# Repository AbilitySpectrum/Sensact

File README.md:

## The Sensact Hub
### An Arduino shield with analog inputs and IR and relay outputs
### - with generic 'sensing' and 'acting' functions configurable by software

#### Features

1. a shield that is compatible with the Arduino board
2. Arduino code that works in tandem with a web based app
3. The web-based app configures the Arduino+Sensact combo
4. Once configured, the combo may be plugged into any USB device for access control
5. The shield also has on-board IR transceivers and is Bluetooth capable

#### Motivation

Existing switch controls for computer users with physical impairment tend to be specialized and expensive. They general use one kind of sensors and have restricted functionality.

We provide a generic device that allows the user to experiment with different sensors, to find something that works best for him. We provide on-board IR output, a socket for an optional Bluetooth board and also configurable key strokes for USB HID controls. 

The Sensact Hub brings together 3 analog inputs (one of them can be configured as an I2C input) and 2 relay outputs as well as HID, IR and Bluetooth outputs.

We use 3.5mm audio sockets to make it easy to swap different input sensors. The tip is VCC, sleeve is GND and Ring is Signal. The first socket can be used by an I2C device where the two rings are SDA and SCL.

#### Use cases

We have used a number of sensors: light, capacitive touch, microphone as touch detectors. The signal can be used to trigger a call bell on one of the relays. Or it can be used to send specific letters over USB to control a smartphone or tablet. With Bluetooth, the hub sends out the letters wirelessly. The IR transceivers can function as a remote control for TV.

We have also been able to plug in a 6DO gyroscope+accelerator module. The user can then use movements to control a mouse.

#### Compatibility:

Board v1 + Arduino v1 + Config v1 or /Serial_port_version

Board v2 + Arduino v1 + Config v1 or /Chrome_version

Board v2 + Arduino v2 + Config v2

#### Set up Config v1

The web-based configuration software is in the *configSensact* directory.

The web-based software requires a serial port server. Its binary is downloadable from <https://github.com/johnlauer/serial-port-json-server>. It is compatible with OSX, Linux and Windows.

#### Set up Config v2

The Config v2 is a Chrome App. The a production release would be downloadable as a Chrome App but it currently must be added as an extension. 

More Tools -> Extensions. Check "Developer Mode". Load unpacked extension. Direct it to the configSensactApp directory.

#### To do
Currently no IR capability.

#### Partners

This work is performed by volunteers and staff at Bruyère's Saint Vincent Hospital AAC Clinic and Nathan Lim from Carleton University, all in Ottawa. 

Bruyère, Carleton and Ability Spectrum are not responsible for the use of this material. Please attribute the source if you republish or use partiallly or in whole, using License below.

#### Disclaimer

All design and code are provided with no warranty whatsoever.

#### License
<https://github.com/abilityspectrum>

Copyright (c) 2015-2016 Ability Spectrum

Permission is hereby granted, free of charge, to any person obtaining a copy
of this software and associated documentation files (the "Software"), to deal
in the Software without restriction, including without limitation the rights
to use, copy, modify, merge, publish, distribute, sublicense, and/or sell
copies of the Software, and to permit persons to whom the Software is
furnished to do so, subject to the following conditions:

The above copyright notice and this permission notice shall be included in
all copies or substantial portions of the Software.

THE SOFTWARE IS PROVIDED "AS IS", WITHOUT WARRANTY OF ANY KIND, EXPRESS OR
IMPLIED, INCLUDING BUT NOT LIMITED TO THE WARRANTIES OF MERCHANTABILITY,
FITNESS FOR A PARTICULAR PURPOSE AND NONINFRINGEMENT. IN NO EVENT SHALL THE
AUTHORS OR COPYRIGHT HOLDERS BE LIABLE FOR ANY CLAIM, DAMAGES OR OTHER
LIABILITY, WHETHER IN AN ACTION OF CONTRACT, TORT OR OTHERWISE, ARISING FROM,
OUT OF OR IN CONNECTION WITH THE SOFTWARE OR THE USE OR OTHER DEALINGS IN
THE SOFTWARE.

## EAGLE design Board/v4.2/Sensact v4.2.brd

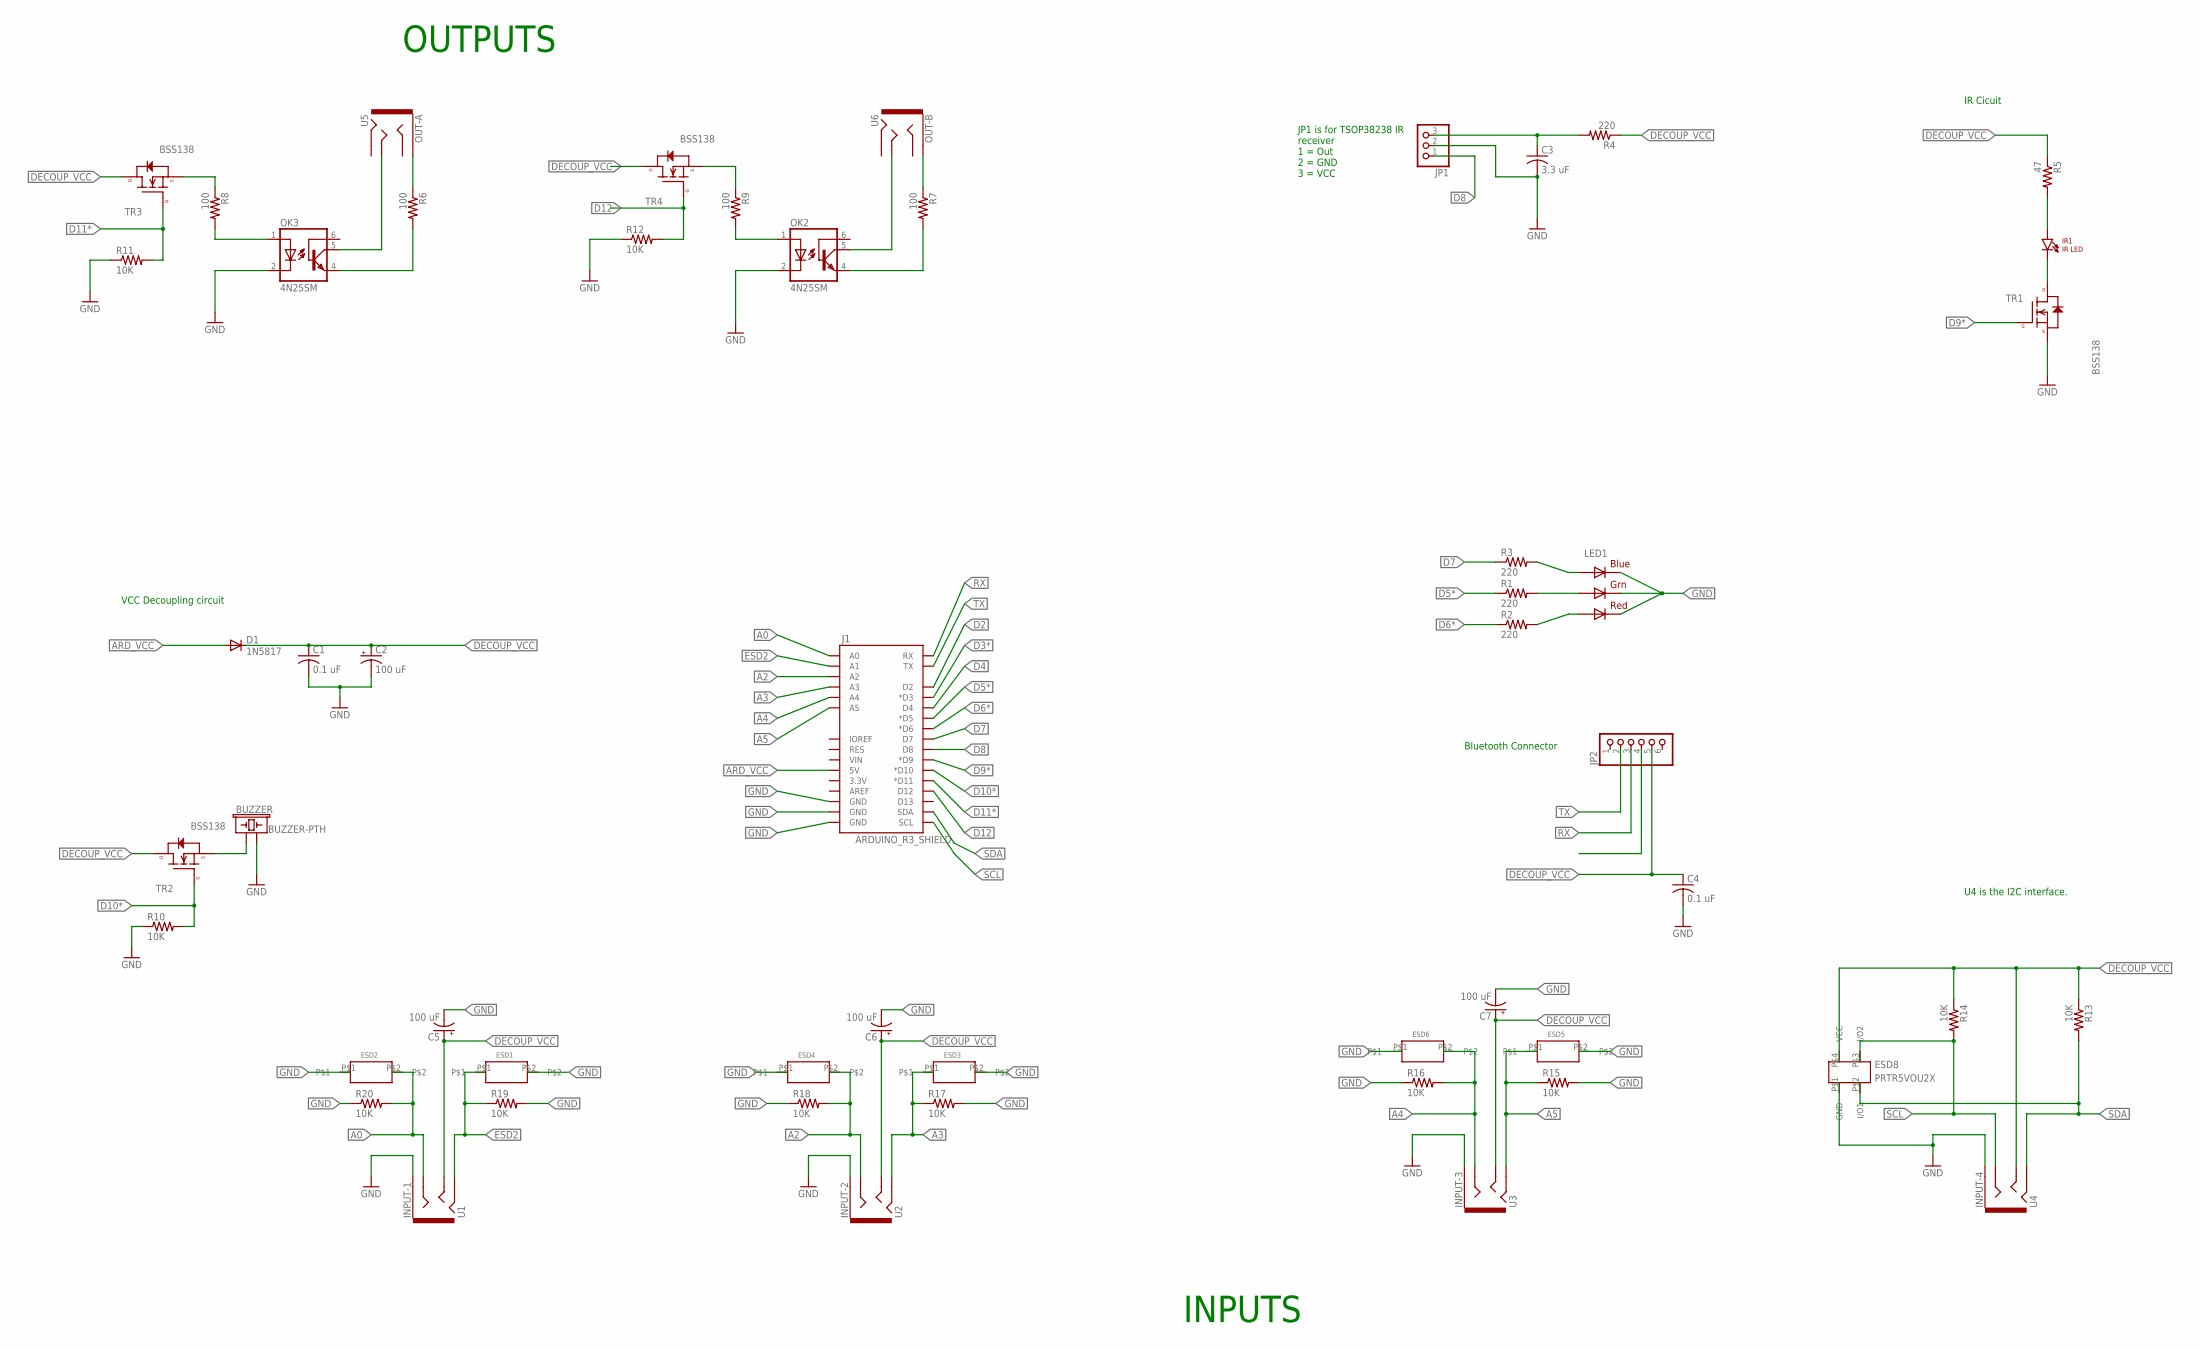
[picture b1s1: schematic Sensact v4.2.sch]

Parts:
BUZZER: BUZZER-PTH; BUZZER-12MM
C1, C4: 0.1 uF; C0805
C2, C5, C6, C7: 100 uF; PANASONIC_C
C3: 3.3 uF; C0805
D1: 1N5817; DO214AC
ESD1, ESD2, ESD3, ESD4, ESD5, ESD6: PESD5V0S1BA; SOD323
ESD8: PRTR5VOU2X; 215
INPUT-1: U1; AUDIO-JACK-TRRS-THRUHOLE
INPUT-2: U2; AUDIO-JACK-TRRS-THRUHOLE
INPUT-3: U3; AUDIO-JACK-TRRS-THRUHOLE
INPUT-4: U4; AUDIO-JACK-TRRS-THRUHOLE
IR1: IR LED; LTE-302
J1: ARDUINO_R3_SHIELD; UNO_R3_SHIELD
JP1: PINHD-1X3; 1X03
JP2: PINHD-1X6; 1X06
LED1: RGBLED5050
OK2, OK3: 4N25SM; DIL6-SMD
OUT-A: U5; AUDIO-JACK-TRRS-THRUHOLE
OUT-B: U6; AUDIO-JACK-TRRS-THRUHOLE
R1, R2, R3, R4: 220; 0805
R5: 47; 0805
R6, R7, R8, R9: 100; 0805
R10, R11, R12, R13, R14, R15, R16, R17, R18, R19, R20: 10K; 0805
TR1, TR2, TR3, TR4: BSS138; SOT23-3

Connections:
A0: ESD2.P$2, INPUT-1.RING1, J1.A0, R20.2
A2: ESD4.P$2, INPUT-2.RING1, J1.A2, R18.2
A3: ESD3.P$1, INPUT-2.RING2, J1.A3, R17.1
A4: ESD6.P$2, INPUT-3.RING1, J1.A4, R16.2
A5: ESD5.P$1, INPUT-3.RING2, J1.A5, R15.1
ARD_VCC: D1.A, J1.5V
D2: J1.D2
D3*: J1.D3 (*D3)
D4: J1.D4
D5*: J1.D5 (*D5), R1.1
D6*: J1.D6 (*D6), R2.1
D7: J1.D7, R3.1
D8: J1.D8, JP1.1
D9*: J1.D9 (*D9), TR1.1 (G)
D10*: J1.D10 (*D10), R10.2, TR2.1 (G)
D11*: J1.D11 (*D11), R11.2, TR3.1 (G)
D12: J1.D12, R12.2, TR4.1 (G)
DECOUP_VCC: C1.1, C2.+, C4.1, C5.+, C6.+, C7.+, D1.C, ESD8.P$4 (VCC), INPUT-1.TIP, INPUT-2.TIP, INPUT-3.TIP, INPUT-4.TIP, JP2.5, R4.1, R5.1, R13.1, R14.1, TR2.3 (D), TR3.3 (D), TR4.3 (D)
ESD2: ESD1.P$1, INPUT-1.RING2, J1.A1, R19.1
GND: BUZZER.- (2), C1.2, C2.-, C3.2, C4.2, ESD1.P$2, ESD2.P$1, ESD3.P$2, ESD4.P$1, ESD5.P$2, ESD6.P$1, ESD8.P$1 (GND), INPUT-1.SLEEVE (EARTH), INPUT-2.SLEEVE (EARTH), INPUT-3.SLEEVE (EARTH), INPUT-4.SLEEVE (EARTH), J1.GND@0 (GND), J1.GND@1 (GND), J1.GND@2 (GND), JP1.2, JP2.4, LED1.4 (BLUE_C), LED1.5 (RED_C), LED1.6 (GREEN_C), OK2.2 (C), OK3.2 (C), R10.1, R11.1, R12.1, R15.2, R16.1, R17.2, R18.1, R19.2, R20.1, TR1.2 (S)
unnamed: C3.1, JP1.3, R4.2
unnamed: OK3.4 (EMI), R6.2
unnamed: OK2.1 (A), R9.2
unnamed: OK3.1 (A), R8.2
unnamed: LED1.3 (BLUE_A), R3.2
unnamed: LED1.1 (GREEN_A), R1.2
unnamed: LED1.2 (RED_A), R2.2
unnamed: OK3.5 (COL), OUT-A.TIP
unnamed: OUT-A.SLEEVE (EARTH), R6.1
unnamed: OK2.5 (COL), OUT-B.TIP
unnamed: OUT-B.SLEEVE (EARTH), R7.1
unnamed: OK2.4 (EMI), R7.2
unnamed: IR1.A, R5.2
unnamed: IR1.C, TR1.3 (D)
unnamed: BUZZER.+ (1), TR2.2 (S)
unnamed: R9.1, TR4.2 (S)
unnamed: R8.1, TR3.2 (S)
RX: J1.RX, JP2.3
SCL: ESD8.P$3 (I/O2), INPUT-4.RING1, J1.SCL, R14.2
SDA: ESD8.P$2 (I/O1), INPUT-4.RING2, J1.SDA, R13.2
TX: J1.TX, JP2.2

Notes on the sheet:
JP1 is for TSOP38238 IR receiver 1 = Out 2 = GND 3 = VCC
VCC Decoupling circuit
U4 is the I2C interface.
OUTPUTS
INPUTS
Bluetooth Connector
IR Cicuit

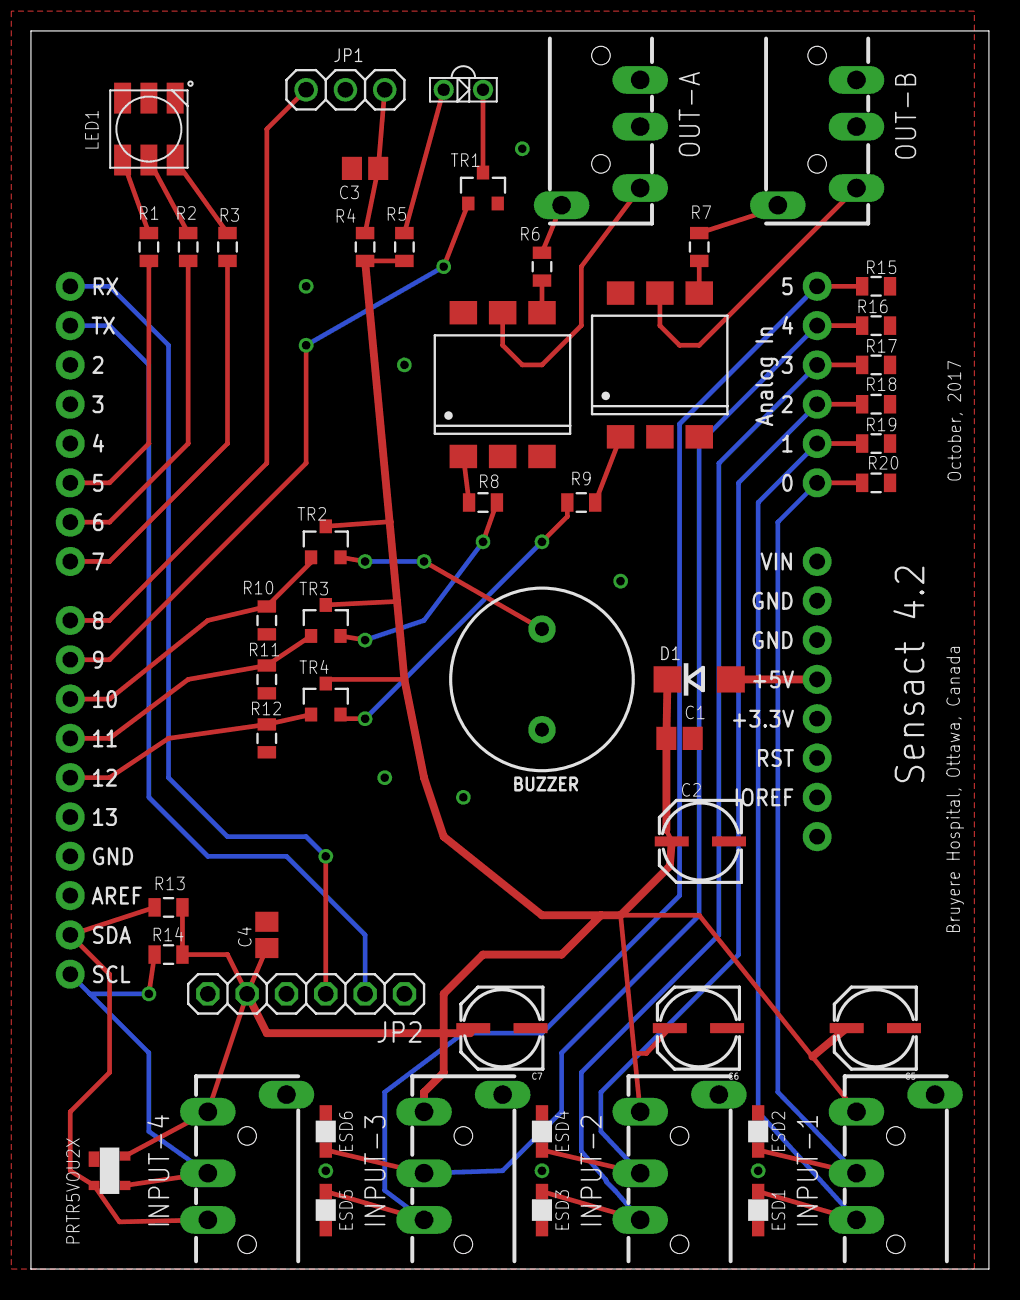
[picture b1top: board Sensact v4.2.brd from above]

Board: 2 copper layers, 61.9 x 80.0 mm, 53 parts (0 on the bottom side), 38 nets.

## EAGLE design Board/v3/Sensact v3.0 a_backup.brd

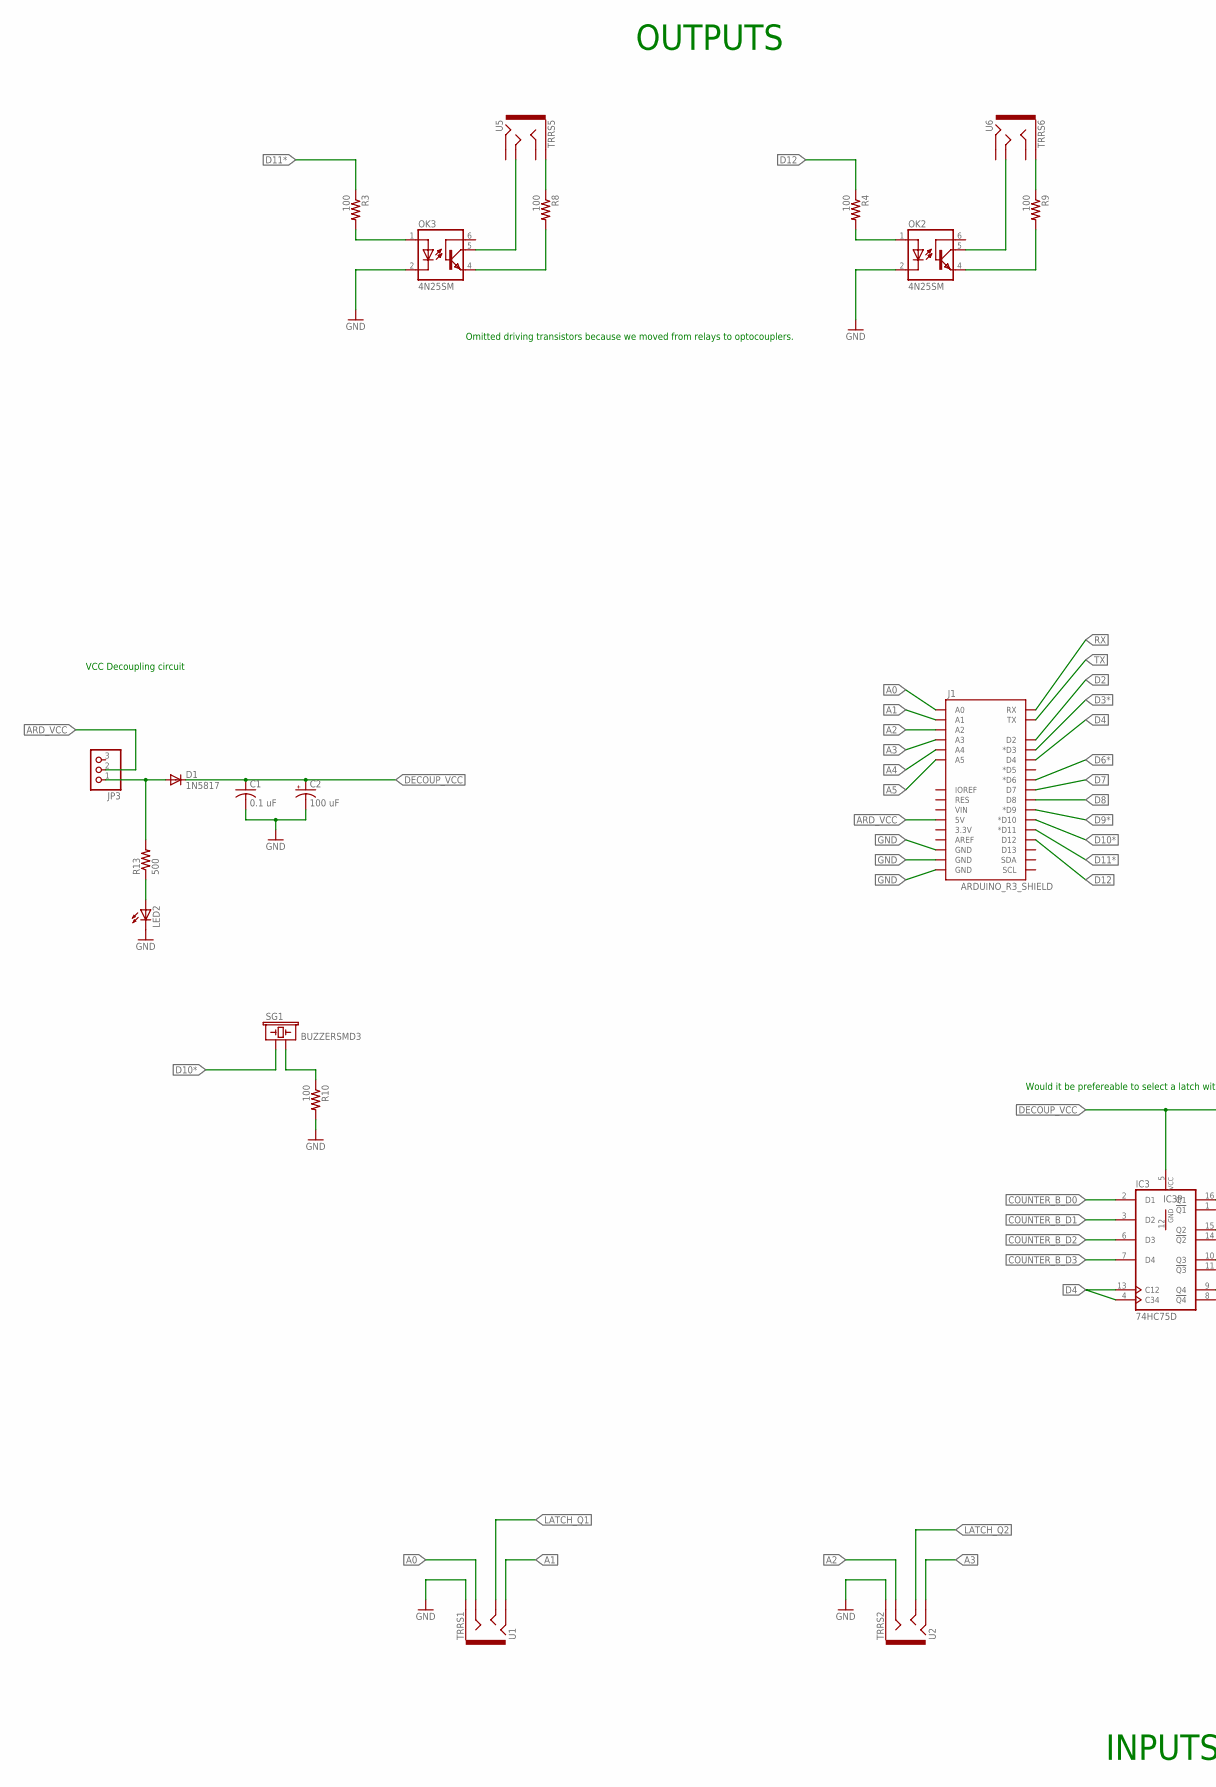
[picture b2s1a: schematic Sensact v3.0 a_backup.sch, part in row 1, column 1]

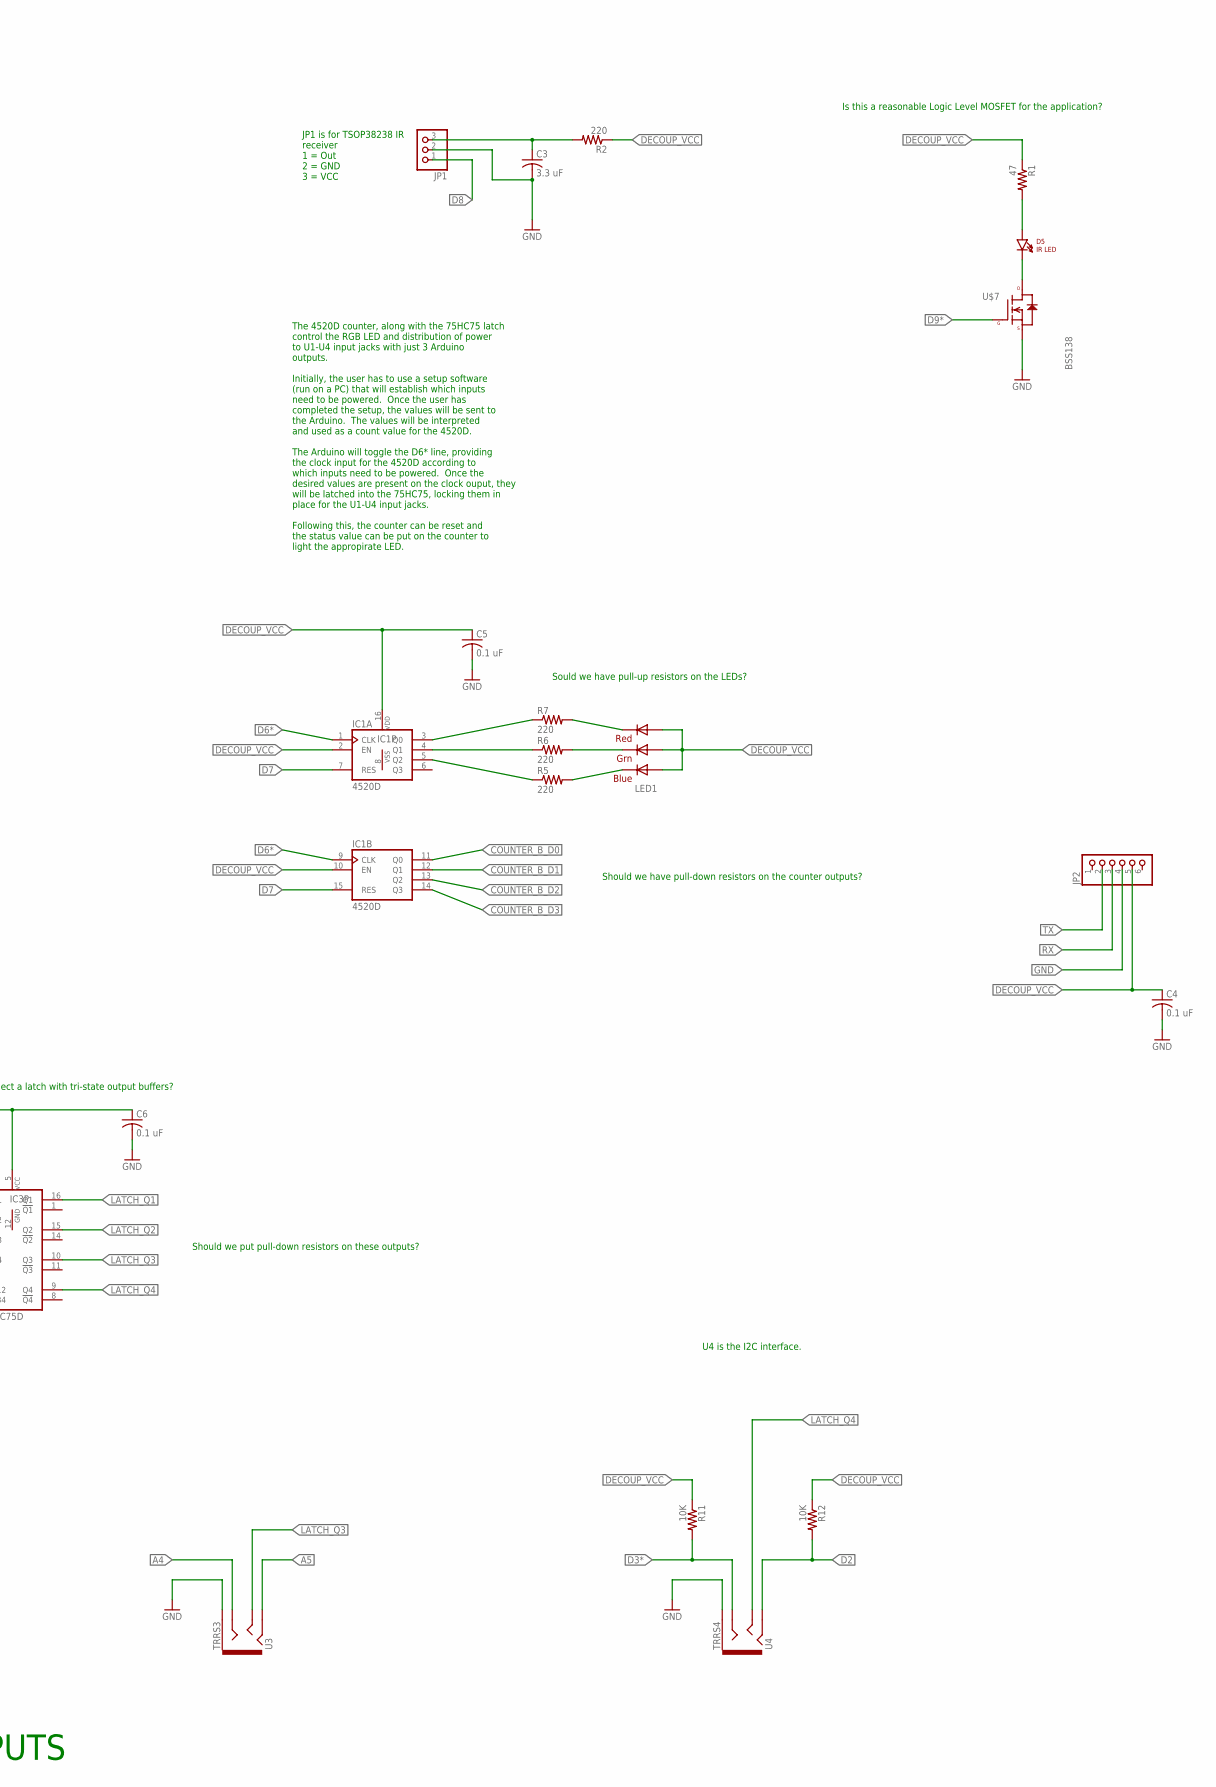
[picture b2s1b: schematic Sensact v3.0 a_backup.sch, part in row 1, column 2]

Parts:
C1, C4, C5, C6: 0.1 uF; C0805
C2: 100 uF; PANASONIC_C
C3: 3.3 uF; C0805
D1: 1N5817; DO214AC
D5: IR LED; LTE-302
IC1: 4520D; SO16
IC3: 74HC75D; SO16
J1: ARDUINO_R3_SHIELD; UNO_R3_SHIELD
JP1, JP3: PINHD-1X3; 1X03
JP2: PINHD-1X6; 1X06
LED1: RGBLED5050
LED2: LEDCHIPLED_0805; CHIPLED_0805
OK2, OK3: 4N25SM; DIL6-SMD
R1: 47; 0805
R2, R5, R6, R7: 220; 0805
R3, R4: 100; 0805
R8, R9, R10: 100; R0805
R11, R12: 10K; 0805
R13: 500; 0805
SG1: BUZZERSMD3; BUZZER-CMT1102
TRRS1: U1; AUDIO-JACK-TRRS-THRUHOLE
TRRS2: U2; AUDIO-JACK-TRRS-THRUHOLE
TRRS3: U3; AUDIO-JACK-TRRS-THRUHOLE
TRRS4: U4; AUDIO-JACK-TRRS-THRUHOLE
TRRS5: U5; AUDIO-JACK-TRRS-THRUHOLE
TRRS6: U6; AUDIO-JACK-TRRS-THRUHOLE
U$7: BSS138; SOT23-3

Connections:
A0: J1.A0, TRRS1.RING1
A1: J1.A1, TRRS1.RING2
A2: J1.A2, TRRS2.RING1
A3: J1.A3, TRRS2.RING2
A4: J1.A4, TRRS3.RING1
A5: J1.A5, TRRS3.RING2
ARD_VCC: J1.5V, JP3.2
COUNTER_B_D0: IC1.11 (Q0), IC3.2 (D1)
COUNTER_B_D1: IC1.12 (Q1), IC3.3 (D2)
COUNTER_B_D2: IC1.13 (Q2), IC3.6 (D3)
COUNTER_B_D3: IC1.14 (Q3), IC3.7 (D4)
D2: J1.D2, R12.2, TRRS4.RING2
D3*: J1.D3 (*D3), R11.2, TRRS4.RING1
D4: IC3.4 (C34), IC3.13 (C12), J1.D4
D6*: IC1.1 (CLK), IC1.9 (CLK), J1.D6 (*D6)
D7: IC1.7 (RES), IC1.15 (RES), J1.D7
D8: J1.D8, JP1.1
D9*: J1.D9 (*D9), U$7.1 (G)
D10*: J1.D10 (*D10), SG1.1
D11*: J1.D11 (*D11), R3.1
D12: J1.D12, R4.1
DECOUP_VCC: C1.1, C2.+, C4.1, C5.1, C6.1, D1.C, IC1.2 (EN), IC1.10 (EN), IC1.16 (VDD), IC3.5 (VCC), JP2.5, LED1.1 (GREEN_A), LED1.2 (RED_A), LED1.3 (BLUE_A), R1.1, R2.1, R11.1, R12.1
GND: C1.2, C2.-, C3.2, C4.2, C5.2, C6.2, IC3.12 (GND), J1.GND@0 (GND), J1.GND@1 (GND), J1.GND@2 (GND), JP1.2, JP2.4, LED2.C, OK2.2 (C), OK3.2 (C), R10.2, TRRS1.SLEEVE (EARTH), TRRS2.SLEEVE (EARTH), TRRS3.SLEEVE (EARTH), TRRS4.SLEEVE (EARTH), U$7.2 (S)
LATCH_Q1: IC3.16 (Q1), TRRS1.TIP
LATCH_Q2: IC3.15 (Q2), TRRS2.TIP
LATCH_Q3: IC3.10 (Q3), TRRS3.TIP
LATCH_Q4: IC3.9 (Q4), TRRS4.TIP
unnamed: C3.1, JP1.3, R2.2
unnamed: R8.1, TRRS5.SLEEVE (EARTH)
unnamed: OK2.1 (A), R4.2
unnamed: OK3.1 (A), R3.2
unnamed: LED1.4 (BLUE_C), R5.2
unnamed: LED1.6 (GREEN_C), R6.2
unnamed: LED1.5 (RED_C), R7.2
unnamed: OK3.5 (COL), TRRS5.TIP
unnamed: OK3.4 (EMI), R8.2
unnamed: OK2.5 (COL), TRRS6.TIP
unnamed: R9.1, TRRS6.SLEEVE (EARTH)
unnamed: LED2.A, R13.1
unnamed: D5.A, R1.2
unnamed: D5.C, U$7.3 (D)
unnamed: OK2.4 (EMI), R9.2
unnamed: D1.A, JP3.1, R13.2
unnamed: R10.1, SG1.2
unnamed: IC1.3 (Q0), R7.1
unnamed: IC1.4 (Q1), R6.1
unnamed: IC1.5 (Q2), R5.1
RX: J1.RX, JP2.3
TX: J1.TX, JP2.2
VSS: IC1.8 (VSS)

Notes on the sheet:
JP1 is for TSOP38238 IR receiver 1 = Out 2 = GND 3 = VCC
VCC Decoupling circuit
U4 is the I2C interface.
OUTPUTS
INPUTS
The 4520D counter, along with the 75HC75 latch control the RGB LED and distribution of power to U1-U4 input jacks with just 3 Arduino outputs. Initially, the user has to use a setup software (run on a PC) that will establish which inputs need to be powered. Once the user has completed the setup, th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
Would it be prefereable to select a latch with tri-state output buffers?
Omitted driving transistors because we moved from relays to optocouplers.
Is this a reasonable Logic Level MOSFET for the application?
Sould we have pull-up resistors on the LEDs?
Should we have pull-down resistors on the counter outputs?
Should we put pull-down resistors on these outputs?

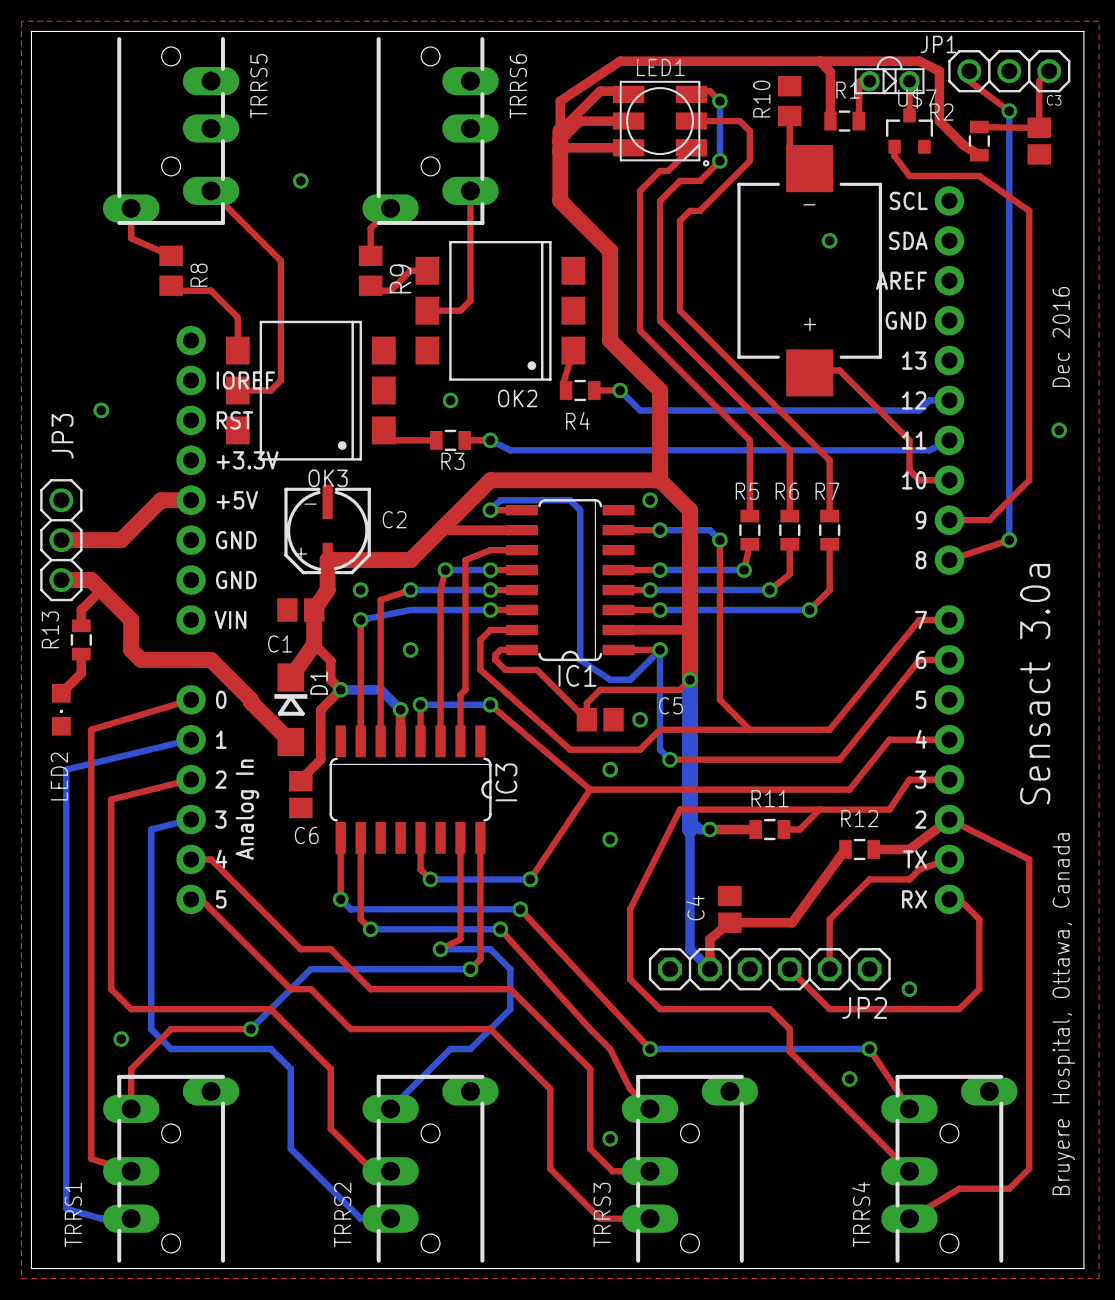
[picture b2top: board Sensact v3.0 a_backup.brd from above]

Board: 2 copper layers, 67.0 x 78.7 mm, 39 parts (0 on the bottom side), 49 nets.

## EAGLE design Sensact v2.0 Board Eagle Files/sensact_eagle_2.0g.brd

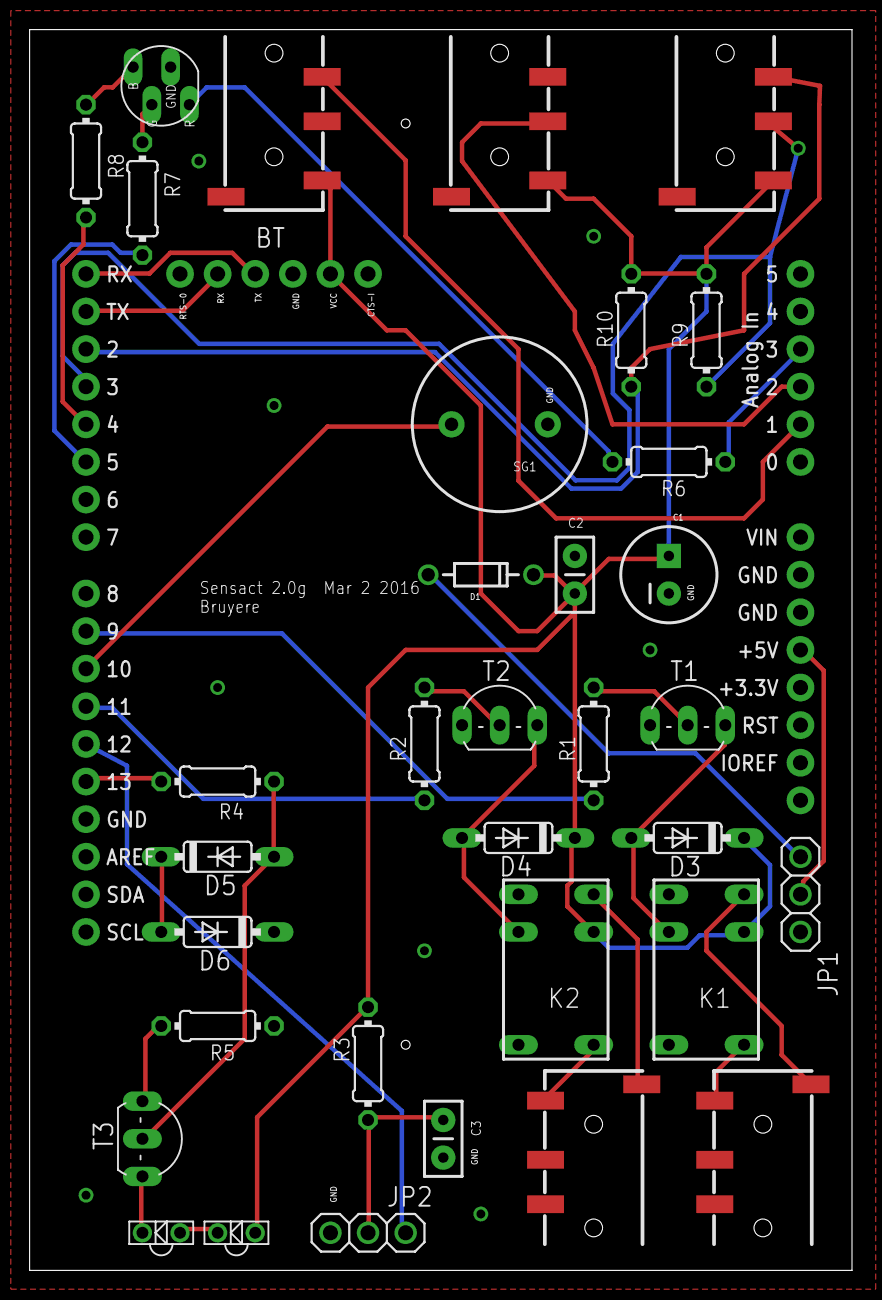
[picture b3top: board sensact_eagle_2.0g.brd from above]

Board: 2 copper layers, 55.5 x 83.8 mm, 36 parts (0 on the bottom side), 35 nets.

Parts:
BT: 1X06_NO_SILK
C1: 100uf; CPOL-RADIAL-100UF-25V
C2: 0.1uf; CAP-PTH-SMALLEZ
C3: 330nf; CAP-PTH-SMALLEZ
D1: DIODE-ZENERPTH; DIODE-ZENER
D3, D4, D5, D6: 1N4148DO35-7; DO35-7
D7, D8: 940nm; LTE-302
D9: OFFSET_RGB_LED_CCOFFSET_RGB_LED_THRU; OFFSET_RGB_THRU
J7: ARDUINO_R3_SHIELD; UNO_R3_SHIELD
JP1, JP2: 1X03
K1, K2: G5V1
R1, R2, R3, R4, R5, R6, R7, R8: 220; 0204/7
R9, R10: 1.5K; 0204/7
SG1: BUZZERPTH; BUZZER-12MM
T1, T2, T3: 2n4401; TO92-EBC
U$1, U$2, U$3, U$4, U$5: AUDIO-JACK3; AUDIO-JACK-TRRS-SMD

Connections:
A1: J7.A1, U$3.RING2
A2: J7.A2, U$2.RING1
A3: J7.A3, R6.1
DECOUP_VCC: BT.5, C1.1, C2.1, D1.P$1, D3.C, D4.C, D7.A, K1.9, K2.9, R3.2, R9.2, R10.2, U$1.TIP, U$2.TIP, U$3.TIP
GND: BT.4, C1.2, C2.2, C3.2, D6.C, D9.2, J7.GND@0, J7.GND@1, J7.GND@2, JP2.1, R5.1, SG1.-, T1.E, T2.E, U$1.EARTH, U$2.EARTH
IO2: J7.D2, R10.1, U$1.RING2
IO3*: J7.D3, R9.1, U$1.RING1
IO4: J7.D4, R8.1
IO5*: J7.D5, R7.1
IO9*: J7.D9, R1.1
IO10*: J7.D10, SG1.+
IO11*: J7.D11, R2.1
IO12: J7.D12, JP2.3
IO13*: J7.D13, R4.1
unnamed: K1.6, U$4.TIP
unnamed: K1.10, U$4.EARTH
unnamed: K2.6, U$5.TIP
unnamed: K2.10, U$5.EARTH
unnamed: D4.A, K2.2, T2.C
unnamed: D3.A, K1.2, T1.C
unnamed: R1.2, T1.B
unnamed: R2.2, T2.B
unnamed: C3.1, JP2.2, R3.1
unnamed: D7.C, D8.A
unnamed: D8.C, T3.C
unnamed: D5.A, R4.2, T3.B
unnamed: R5.2, T3.E
unnamed: D9.3, R7.2
unnamed: D5.C, D6.A
unnamed: D9.1, R6.2
unnamed: D9.4, R8.2
RX: BT.3, J7.RX
SW_VCC: D1.P$2, JP1.1
TX: BT.2, J7.TX
VCC: J7.5V, JP1.2

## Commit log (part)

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2016-03-28 Baseline code
    the Arduino version works with v1 of the Sensact board with the Pro
    Micro board
2016-04-11 modes for Sensact v2
    - local p5 files
    - #ifdefs for the two versions
    - remove gyro capabilities for now
2016-04-13 added click, joystick
    - joystick control complete
    - click implemented but not interfaced
2016-04-17 update
    - use INCLUDE_MPU etc to include mouse actions
    - otherwise it is normal Sensact
    - INPUT 1 does not work
    - cannot have include mouse in normal Sensact for lack of code space
2016-05-07 - change index.html -> configSensact.html - added REFRACTORY period after trigger - bug fix: RELAY_? -> SENSACT_OUT?
2016-05-27 updated app readme for installation procedure
2016-05-30 Initial commit of board design files
    These are the board design files for the board produced in April 2016.
    The Gerber files were placed in a subdirectory for simplicity.
2016-06-06 added functional doc, altered sensact arduino send config package
2016-06-06 mimic old config software
2016-06-10 Added sensact func doc v2
2016-06-10 update func doc2
2016-06-17 Test program to be used following assembly
    This program tests the following functions:
    Beeper, Bluetooth, LED, and switch connected to D7
2016-06-21 changed mouse control
    - geninput: changed mouse control to use initial values for ‘zero’
    - sensact: now include output box
2016-06-21 minor geininput update
2016-06-22 adding multiple thresholds
2016-06-23 arduino code can do multiple triggers per sensor. Also, can differentiate a long and short click.
2016-06-23 EEPROM read and writing works
2016-06-29 example commit
2016-06-30 New Arduino code can now do buzzer, bluetooth HID, relays, keboard, and mouse. It is ready to be tested
2016-07-18 serial port fix attempt
2016-07-18 merge
2016-07-26 updated sensact app to display sensors over threshold range slider
2016-07-26 debug fixed
2016-07-27 long clicks should work
2016-07-27 long and short click function, can set long click time
2016-07-28 added Enclosures/v1 and Documents/ISAAC_2016
2016-07-28 testing simplified triggers
2016-08-04 Config: fixed invert, changed some gui labels, port display now scrolls. \nArduino: fixed bluetooth communication errors, added mouse speed macro
2016-08-04 added bluno beetle code for Gyro Mouse
2016-09-13 added beetle headmouse readme
2016-09-27 changes to geninput
    modified joystick speed
2016-11-14 v3 board schematic added incorrectly, fixing...
2016-11-14 Adding v3 schematic for comment
2016-11-23 Version 3 Configuration code
    Complete working configuration code. serial-port-json-server is
    required to make this work.
2016-11-24 Bruyere TV Codes
    Added IR codes for Bruyere's Toshiba TVs.
2016-11-25 Improve navigation
    Make the input names more obviously clickable. Change color on hover,
    add a triangle to suggest something will open, and use a cursor pointer.
2016-11-26 Data transfer document
    Add the data transfer document.
2016-11-27 More IO adjustments.
    Corrections for negative number handling. Also add blank to the set of
    chars ignored as white space.
2016-12-02 Errors reading repeat values.
    When getting values from Sensact repeat was not being handled correctly.
2016-12-02 "Keyboard" cmd from PC - PC side
    These files define a new web page with buttons. The page also uses
    serial.js.
2016-12-02 Committing Eagle files for Sensact 3.0a
    Board layout, schematic, and accompanying .pdfs. Also included Gerber
    files.
2016-12-02 Display char value for PC Keyboard sensor.
    Use the character value, rather than character code in the Keyboard
    trigger. This is much easier for those customizing the function, since
    character values have to match those in keybdcontrol.html
2016-12-02 Added a comment
2016-12-04 Fixed a small bug.
    code was treating svalue as a string - thus -243 + 1 was giving -2431
    instead of -242.
2016-12-17 minor update to geninput
2017-01-15 Make mouse-button typing faster.
    Make mouse move faster as repeat action is continued.
2017-01-15 Mouse action completion
    Should have been in the previous check-in. Makes repeated actions
    repeat faster as they are held longer.
2017-01-15 Change ANY trigger action.
    Do not trigger the ANY state trigger if sensor is already in the action
    state.
2017-01-22 Trigger overrun protection
2017-01-23 Interface.js rewrite
    Creation of utilities.js and rewrite of interface.js to make the code
    easier to maintain.
2017-01-24 Oops!
    Left the code in debug mode. Need to fix that.
2017-02-25 Added library to control robot
2017-04-04 my defines
    gendisplay displays 6 analog values
2017-04-04 added latches code (for debugging v3 hardware)
2017-04-10 Melanie B
    4 button “cross”
2017-04-10 melanie A
    - trying to recover old version
    - change its speed to faster pace
    - unfinished
2017-04-10 remove some keys as they are not needed
2017-04-17 Allow keyboard input up to 4 chars
    For HID keyboard input allow the parameter (a long) to hold up to 4
    character values.
2017-04-20 Enhancements to test program.
    Repeated reading of pins.
    Gyro I2C support.
2017-04-21 IR Testing
    Added 't' option for IR circuit testing.
2017-04-22 Us Pull ups on analog inputs
    Us pull up resistors so unconnected inputs do not float. This was also
    needed to make TASH switch work.
2017-04-22 Safety Reset
    When new triggers are loaded reset all triggers, actions and sensors.
    Unfortunately this consumed a bit of memory space and the max # of
    triggers has had to be reduced to 18.
2017-05-10 Fix buzzer logic bug.
2017-05-10 Memory Saved Trick #1
    Hold times in unsigned int instead of long and handle the rollover.
    Saves 4 byte per trigger = 80 bytes.
2017-05-10 Discussion of State Machines
2017-05-10 Memory Saving Trick #3
    Pack values of <= 15 into half of a char.
    Savings is 3 chars per trigger = 60 bytes.
2017-05-11 Tidy up
2017-05-11 Get Connection box completely off the screen.
    The connection box can be big if there are a lot of serial ports to
    choose from. Make the move distance dynamic so we always clear the
    window.
2017-05-12 Increased Mouse Support
    Bluetooth mouse. Press / Release / Right Click for HID and BT.
2017-05-18 Special Key Support
2017-05-28 Keyboard Control classes
    Make keyboard control class structure similar to Mouse control. Also,
    fix a timing bug in the general repeat-action code.
2017-05-29 Increase relay pulse width.
    This makes the call bell work.
2017-06-20 Minor updates to test code.
2017-06-21 LED color correction
    Get the LED colors to display correctly.
2017-08-09 Get all 'Solutions' working
    Finish the coding for the solutions.
2017-08-18 Support IDLE mode
2017-08-18 SetState action support
    Allows one sensor to alter the state of another.
2017-09-04 Mouse Stop added
2017-09-14 Test Code for V4.1 Hardware
    Changed the name of the folder and program to be generic, as well as
    updating the code and documentation for V4.1.
2017-09-14 Arduino code update for V4.1
    Basic operation has been confirmed. Detailed testing should still be
    done.
2017-09-27 Drop .pyc files.
    They should not have been promoted in the first place.
2017-09-29 Correct handling of numeric entry.
    Dealt with problems caused by clicking on drop-downs, or tabs. It got a
    bit messy.
2017-09-30 Refinements to numeric entry
    If user enters a value too small, force to smallest allowed value. Same
    idea with numbers too bit.
2017-10-26 Stop runaway mouse repeat actions.
    If sensor value has been near 0 for 15 seconds assume it is
    disconnected.
2017-10-28 Improved runaway mouse fix.
    Sensors are assumed DISCONNECTED until a non-zero signal is detected.
    This means no runaway mouse at all on startup.
2017-10-29 Runaway mouse #3
    Allow for negative values too - e.g. from gyro.
2017-11-11 Handle lost connection
    If serial connection is lost allow user to try to re-establish it.
2017-11-12 Fix Trigger Creation Lock-up
    Trigger creation used to lock up during display mode. Made the conflict
    time for triggerLock much shorter.
    Also, removed some debug statements in SAMain.py
2017-12-05 Mouse Speed Control
    Adds the ability to change the speed of mouse motion.
2017-12-05 UI Wording improvement
2017-12-23 Various config bug fixes
    An attempt to fix problems found on the Mac.
2018-01-02 Mac Fixes for Config
2018-01-24 Initial work on ATMega support.
    Not fully tested yet. Big issue - does not work with Bluetooth!! I2C
    is OK. IR is untested.
2018-02-07 Add IRLib to repository
2018-02-19 Added mouse speed info to data transfer document.
2018-02-19 Java Version - First Promotion
2018-02-22 Support for Solutions
2018-03-01 Some minor UI improvements and code adjustments.
2018-03-05 Various UI adjustments
    Also, made ActionName an ENUM rather than just a String. Allows for
    more robust error checking.
2018-03-28 I18N Model resources
    Isolate sensor and action related strings to a resource file.
2018-04-04 Relay Options
    Relay ON and OFF options added.
2018-04-08 Update test procedures
2018-04-08 V4.2 board design
2018-05-04 Write to serial for Mac
    Write no more than 300 bytes at a time.
2018-05-22 Change INPUT to SENSOR
2018-05-29 Mac support for serial write.
    Add a delay for serial write - Mac needs it.
2018-05-29 Key shortcuts for Run and Idle
2018-05-30 New tones on Save
    Now success is signalled by two high beeps.
    Failure by a low raspberry.
2018-05-31 Added Schematic.pdf
2018-06-18 Correction
2018-08-03 Migration to IRLib2 - made changes necessary to use IRLib2 library rather than IRLib, which has been deprecated for future development
2018-09-13 Key Press Config Changes
2018-09-13 Key Press and Mem Check Changes
2018-09-25 Increase to 35 triggers.
2018-10-25 Minor test improvement
    Added more tones to buzzer test.
2018-10-28 Moved Files
2018-10-28 deleted private.xml
2018-10-28 git ignore changed
2018-10-28 Move deliverable directory
2018-10-28 License header added to Arduino code
2018-10-28 Java code license header
2018-10-29 Prototype ADS1015 support
2018-10-29 Ignore java build directory.
2018-10-31 Documentation Update
2018-11-01 Add trigger count to UI
2018-12-03 New IR Lib
2018-12-03 Arduino changes
2019-01-17 I18N - Phase 1
    Internationalization of model directory
    Allow language and country codes on command line.
2019-01-17 I18N - Phase 1 - Ooops
2019-01-23 I18N Phase 3 - Solutions
    Solutions I18N
2019-02-05 Fix bugs in USB Port handling
2019-02-05 USB Port bug fix
2019-02-21 UI internationalization
    Move all strings in the UI directory into strings.properties
2019-02-21 Completed I18N
    Deliverable jar file contains Spanish translation files.
2019-02-23 added translations in strings_es.properties
2019-05-13 Integrate resource files into the build process.
    Now a build adds the necessary resource files to the dist directory and
    loads the Spanish properties files into the jar file.
2019-05-13 Minor test correction.
2019-05-15 Cut and Paste for Sensact Config
2019-05-15 More options for SerialFeedback
    Configurable display time and title bar.
2019-06-02 LED Display Code
    Supports Don's LED screen as a means to provide visual feedback.
2019-06-03 Minor bug fix.
    Sensor levels were not being copied correctly. Error was introduced
    when implementing copy/paste.
2019-06-03 Jar file update
2019-06-07 LED_Display changed to LCD_Display
2019-11-18 Update JAR file for BT Special

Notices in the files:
parts and their libraries:
SparkFun-Capacitors: Licensing: Creative Commons ShareAlike 4.0 International - https://creativecommons.org/licenses/by-sa/4.0
